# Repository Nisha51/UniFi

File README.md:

**UniFi**

The UniFi is a 36 key split keyboard, that unifies almost all the features found in modern boards in a compact PCB.

It has,
1. OLED and nice!view support.
2. Encoder support.
3. Piezo buzzer support.
4. Both wireless and wired support.
5. Per key RGB with support for underglow.

This keyboard was inspired by the FiFi keyboard

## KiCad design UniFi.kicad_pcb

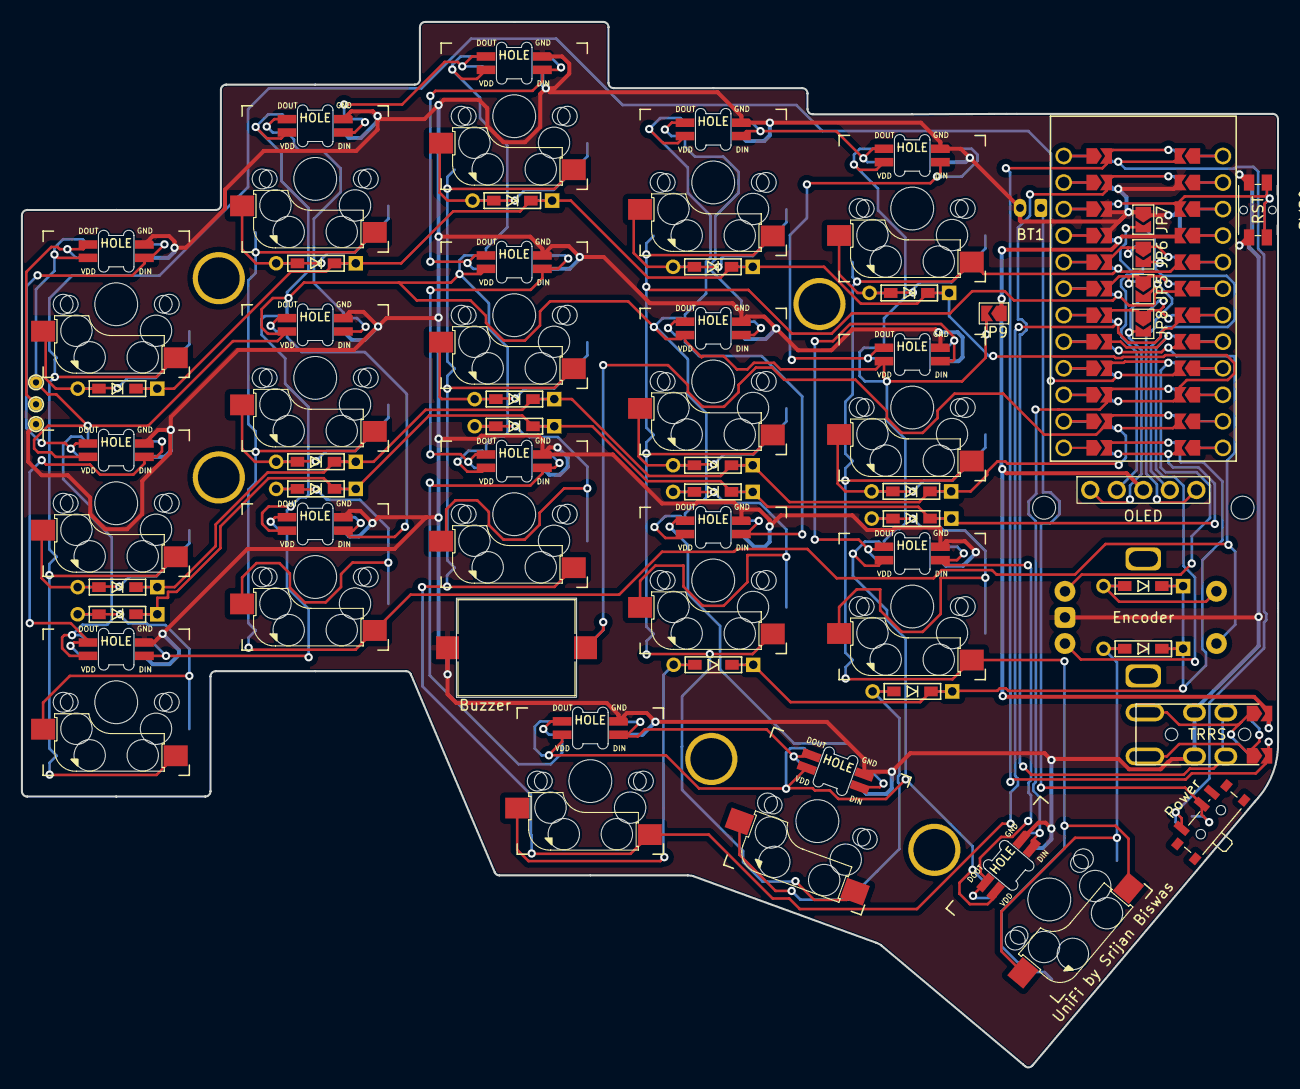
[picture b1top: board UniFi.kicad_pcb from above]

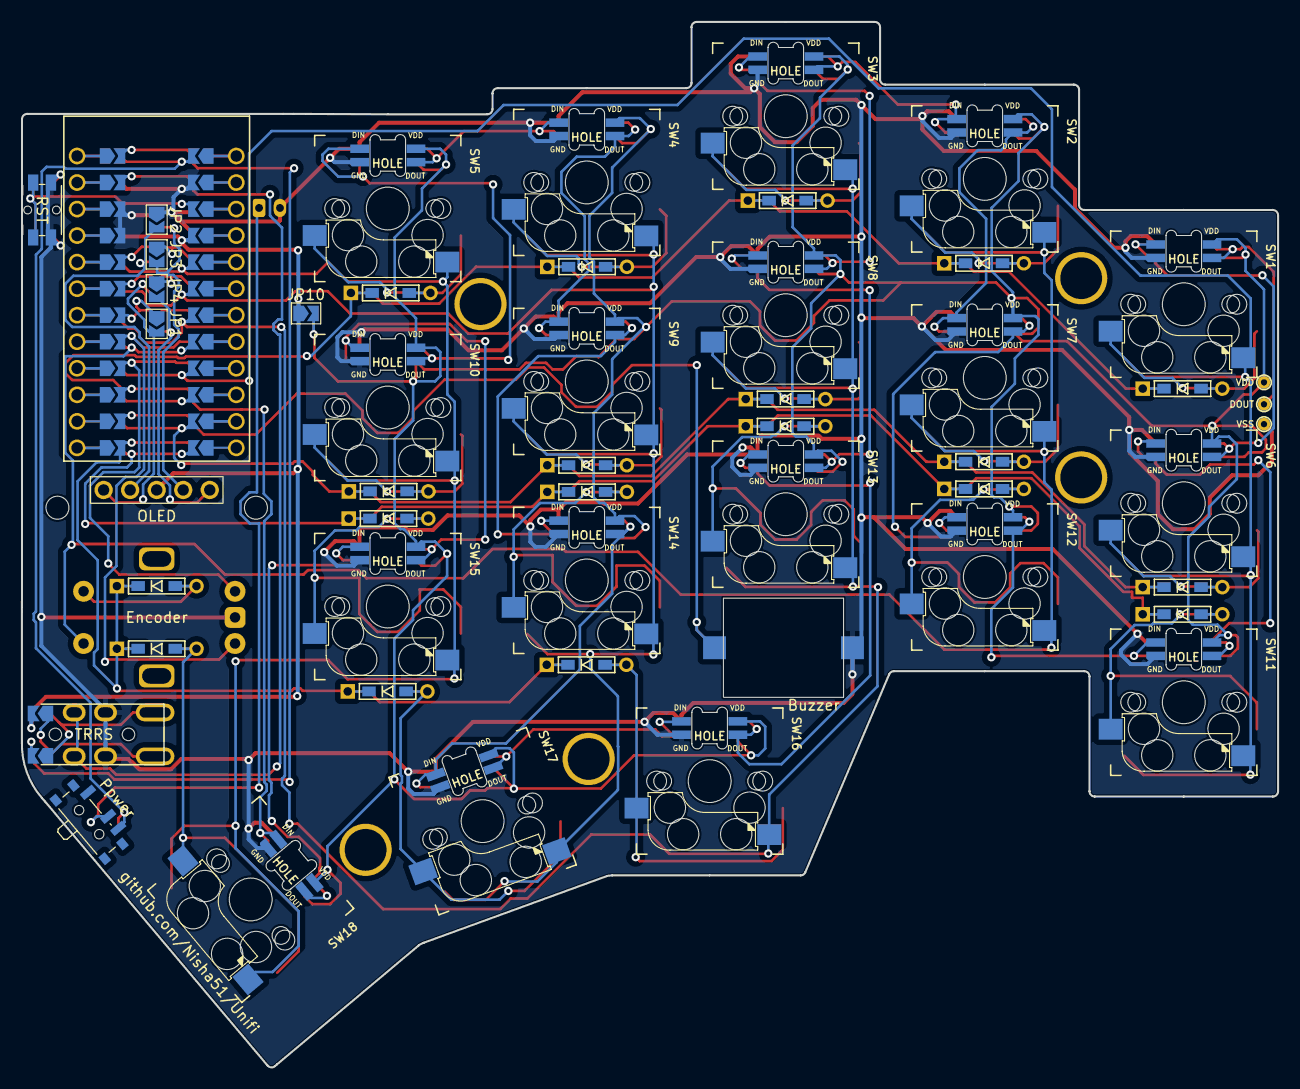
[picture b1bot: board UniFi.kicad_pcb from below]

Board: 2 copper layers, 120.2 x 100.1 mm, 67 parts (7 on the bottom side), 65 nets.

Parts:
BT1: Battery; JST_PH_S2B-PH-K_1x02_P2.00mm_Horizontal
BZ1: Buzzer; Buzzer_Mallory_AST1109MLTRQ
D1, D2, D3, D4, D5, D6, D7, D8, D9, D10, D11, D12, D13, D14, D15, D16, D17, D18, D19: D; D3_TH_SMD
H1, H2, H3, H4, H5: MountingHole; M2_Hole_TH_Outside
H6, H7: MountingHole; MountingHole_2.2mm_M2
J1: OLED; nice_view
J2: MJ-4PP-9 TRRS; PJ-320A
JP1, JP2, JP3, JP4, JP5, JP6, JP7, JP8, JP9, JP10: Device_Jumper_NO_Small; SolderJumper-2_P1.3mm_Open_TrianglePad1.0x1.5mm
Power: SW_SPDT; SW_SPDT_PCM12
Ppwer: SW_SPDT; SW_SPDT_PCM12
SW1, SW2, SW3, SW4, SW5, SW6, SW7, SW8, SW9, SW10, SW11, SW12, SW13, SW14, SW15, SW16, SW17, SW18: SW_PUSH-MX_W_LED; SK6812MINI_e_and_cherry
SW19: RotaryEncoder_Switch; ROT_Alps_EC11E-Switch
SW20, SW21: Push_Button; Panasonic_EVQPUL_EVQPUC
TP1: VDD; TestPoint
TP2: DOUT; TestPoint
TP3: VSS; TestPoint
U1: ProMicro_NiceNano_EliteC; ProMicro_unrouted_flipped

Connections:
AUDIO: BZ1.1 (-), U1.11 (B4)
BAT+: Power.1 (A), Ppwer.3 (C), U1.24 (B0/VBUS)
COL1: SW1.6, SW6.6, SW11.6, U1.16 (B1)
COL2: SW2.6, SW7.6, SW12.6, SW19.S1, U1.17 (F7)
COL3: SW3.6, SW8.6, SW13.6, SW16.6, U1.18 (F6)
COL4: SW4.6, SW9.6, SW14.6, SW17.6, U1.19 (F5)
COL5: SW5.6, SW10.6, SW15.6, SW18.6, U1.20 (F4)
CS: JP1.1, JP8.1, U1.7 (D4)
ECA: SW19.A, U1.9 (D7)
ECB: SW19.B, U1.8 (C6)
ECR: D19.2 (A), SW19.S2
GND: BT1.2 (-), BZ1.2 (+), J2.4, JP2.1, JP7.1, SW1.3 (GND), SW2.3 (GND), SW3.3 (GND), SW4.3 (GND), SW5.3 (GND), SW6.3 (GND), SW7.3 (GND), SW8.3 (GND), SW9.3 (GND), SW10.3 (GND), SW11.3 (GND), SW12.3 (GND), SW13.3 (GND), SW14.3 (GND), SW15.3 (GND), SW16.3 (GND), SW17.3 (GND), SW18.3 (GND), SW19.C, SW20.2, SW21.2, TP3.1, U1.3 (GND), U1.4 (GND), U1.23 (GND)
LED: SW18.4 (DIN), U1.10 (E6)
unnamed: BT1.1 (+), Power.2 (B), Ppwer.2 (B)
unnamed: D1.2 (A), SW1.5
unnamed: D2.2 (A), SW2.5
unnamed: D3.2 (A), SW3.5
unnamed: D4.2 (A), SW4.5
unnamed: D5.2 (A), SW5.5
unnamed: D6.2 (A), SW6.5
unnamed: D7.2 (A), SW7.5
unnamed: D8.2 (A), SW8.5
unnamed: D9.2 (A), SW9.5
unnamed: D10.2 (A), SW10.5
unnamed: D11.2 (A), SW11.5
unnamed: D12.2 (A), SW12.5
unnamed: D13.2 (A), SW13.5
unnamed: D14.2 (A), SW14.5
unnamed: D15.2 (A), SW15.5
unnamed: D16.2 (A), SW16.5
unnamed: D17.2 (A), SW17.5
unnamed: D18.2 (A), SW18.5
unnamed: J1.1, JP4.2, JP8.2
unnamed: J1.2, JP3.2, JP7.2
unnamed: J1.4, JP2.2, JP6.2
unnamed: J1.5, JP1.2, JP5.2
unnamed: SW1.4 (DIN), SW6.2 (DOUT)
unnamed: SW1.2 (DOUT), TP2.1
unnamed: SW2.4 (DIN), SW3.2 (DOUT)
unnamed: SW2.2 (DOUT), SW7.4 (DIN)
unnamed: SW3.4 (DIN), SW8.2 (DOUT)
unnamed: SW4.4 (DIN), SW5.2 (DOUT)
unnamed: SW4.2 (DOUT), SW9.4 (DIN)
unnamed: SW10.4 (DIN), SW15.2 (DOUT)
unnamed: SW5.4 (DIN), SW10.2 (DOUT)
unnamed: JP9.2, JP10.2, SW1.1 (VDD), SW2.1 (VDD), SW3.1 (VDD), SW4.1 (VDD), SW5.1 (VDD), SW6.1 (VDD), SW7.1 (VDD), SW8.1 (VDD), SW9.1 (VDD), SW10.1 (VDD), SW11.1 (VDD), SW12.1 (VDD), SW13.1 (VDD), SW14.1 (VDD), SW15.1 (VDD), SW16.1 (VDD), SW17.1 (VDD), SW18.1 (VDD), TP1.1
unnamed: SW11.4 (DIN), SW12.2 (DOUT)
unnamed: SW6.4 (DIN), SW11.2 (DOUT)
unnamed: SW7.2 (DOUT), SW12.4 (DIN)
unnamed: SW13.4 (DIN), SW16.2 (DOUT)
unnamed: SW8.4 (DIN), SW13.2 (DOUT)
unnamed: SW9.2 (DOUT), SW14.4 (DIN)
unnamed: SW14.2 (DOUT), SW17.4 (DIN)
unnamed: SW15.4 (DIN), SW18.2 (DOUT)
unnamed: SW16.4 (DIN), SW17.2 (DOUT)
RESET: SW20.1, SW21.1, U1.22 (RST)
ROW1: D1.1 (K), D2.1 (K), D3.1 (K), D4.1 (K), D5.1 (K), U1.15 (B3)
ROW2: D6.1 (K), D7.1 (K), D8.1 (K), D9.1 (K), D10.1 (K), U1.14 (B2)
ROW3: D11.1 (K), D12.1 (K), D13.1 (K), D14.1 (K), D15.1 (K), U1.13 (B6)
ROW4: D16.1 (K), D17.1 (K), D18.1 (K), D19.1 (K), U1.12 (B5)
RX: J2.2, U1.2 (RX)
SCL: JP3.1, JP6.1, U1.5 (SCL)
SDA: JP4.1, JP5.1, U1.6 (SDA)
TX: J2.1, U1.1 (TX)
VCC: J1.3, J2.3, JP9.1, JP10.1, U1.21 (VCC)

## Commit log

2024-04-25 Updated pcb
2024-04-25 Updated TRRS
2024-05-25 Added Plates
2024-06-06 Updated Plate
2024-06-12 Updated pins
2024-06-23 Added References
